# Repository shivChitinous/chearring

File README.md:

# chearring

Project to generate <1 cm charlieplexed grid of leds with ch32v003 based on https://mitxela.com/projects/ledstud. 

Project designed in Autodesk Fusion with schematic design in KiCad based on code from [kikad-skip](https://github.com/psychogenic/kicad-skip). 

Includes an Autodesk/EAGLE library with symbols, footprints and 3d designs for the following components: 

1. ### CH32V003F4U6 (QFN20)
2. ### 0201 LED
3. ### 0603 SMD capacitor

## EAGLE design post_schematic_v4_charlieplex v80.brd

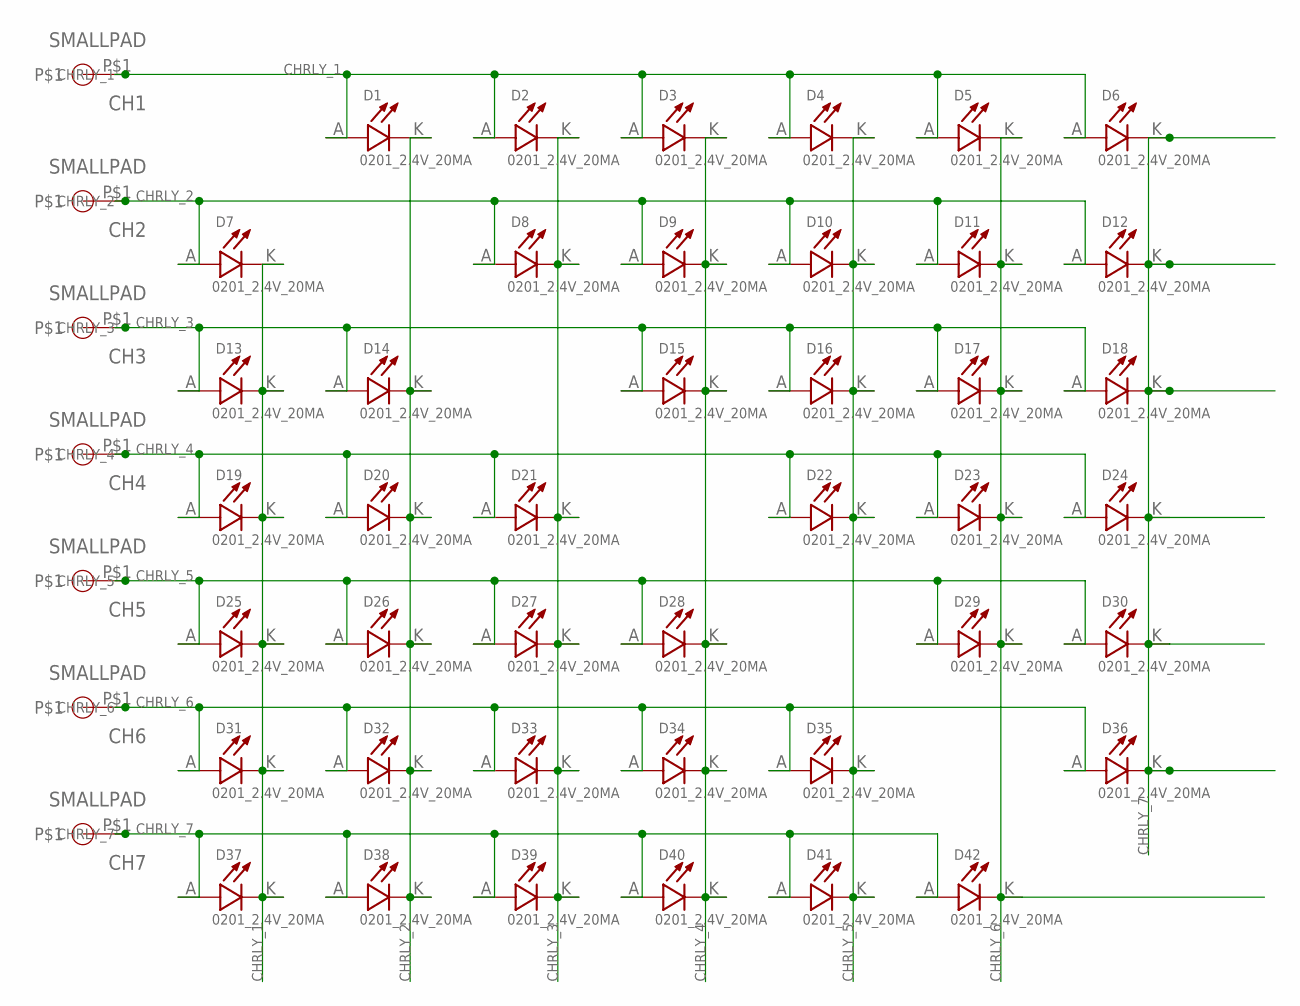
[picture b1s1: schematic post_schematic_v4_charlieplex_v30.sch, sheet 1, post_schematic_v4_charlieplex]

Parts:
CH1, CH2, CH3, CH4, CH5, CH6, CH7: SMALLPAD
D1, D2, D3, D4, D5, D6, D7, D8, D9, D10, D11, D12, D13, D14, D15, D16, D17, D18, D19, D20, D21, D22, D23, D24, D25, D26, D27, D28, D29, D30, D31, D32, D33, D34, D35, D36, D37, D38, D39, D40, D41, D42: 0201_2.4V_20MA

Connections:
CHRLY_1: CH1.P$1, D1.A, D2.A, D3.A, D4.A, D5.A, D6.A, D7.K, D13.K, D19.K, D25.K, D31.K, D37.K
CHRLY_2: CH2.P$1, D1.K, D7.A, D8.A, D9.A, D10.A, D11.A, D12.A, D14.K, D20.K, D26.K, D32.K, D38.K
CHRLY_3: CH3.P$1, D2.K, D8.K, D13.A, D14.A, D15.A, D16.A, D17.A, D18.A, D21.K, D27.K, D33.K, D39.K
CHRLY_4: CH4.P$1, D3.K, D9.K, D15.K, D19.A, D20.A, D21.A, D22.A, D23.A, D24.A, D28.K, D34.K, D40.K
CHRLY_5: CH5.P$1, D4.K, D10.K, D16.K, D22.K, D25.A, D26.A, D27.A, D28.A, D29.A, D30.A, D35.K, D41.K
CHRLY_6: CH6.P$1, D5.K, D11.K, D17.K, D23.K, D29.K, D31.A, D32.A, D33.A, D34.A, D35.A, D36.A, D42.K
CHRLY_7: CH7.P$1, D6.K, D12.K, D18.K, D24.K, D30.K, D36.K, D37.A, D38.A, D39.A, D40.A, D41.A, D42.A

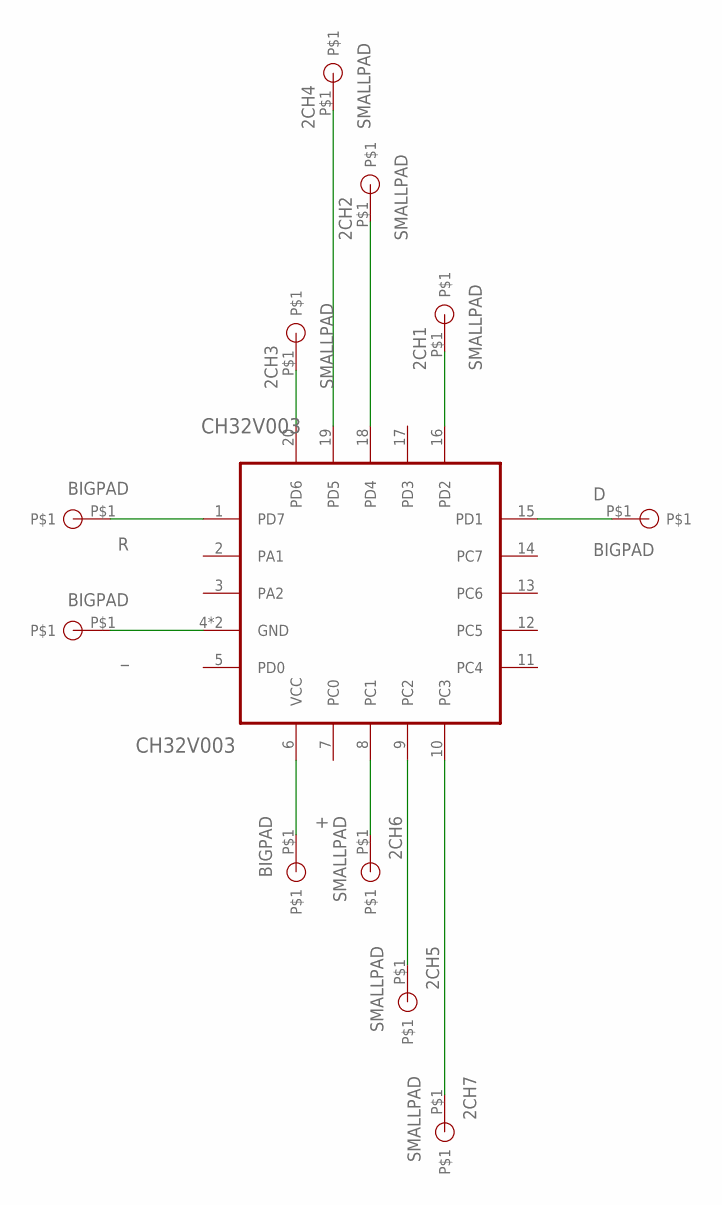
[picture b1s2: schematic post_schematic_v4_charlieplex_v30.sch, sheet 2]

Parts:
2CH1, 2CH2, 2CH3, 2CH4, 2CH5, 2CH6, 2CH7: SMALLPAD
+: BIGPAD
CH32V003: CH32V003; QFN40P300X300X90-21N
D: BIGPAD
R: BIGPAD
_: BIGPAD

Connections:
unnamed: +.P$1, CH32V003.6 (VCC)
unnamed: CH32V003.4 (GND), CH32V003.21 (GND), _.P$1
unnamed: CH32V003.1 (PD7), R.P$1
unnamed: CH32V003.15 (PD1), D.P$1
unnamed: 2CH1.P$1, CH32V003.16 (PD2)
unnamed: 2CH2.P$1, CH32V003.18 (PD4)
unnamed: 2CH3.P$1, CH32V003.20 (PD6)
unnamed: 2CH4.P$1, CH32V003.19 (PD5)
unnamed: 2CH6.P$1, CH32V003.8 (PC1)
unnamed: 2CH5.P$1, CH32V003.9 (PC2)
unnamed: 2CH7.P$1, CH32V003.10 (PC3)

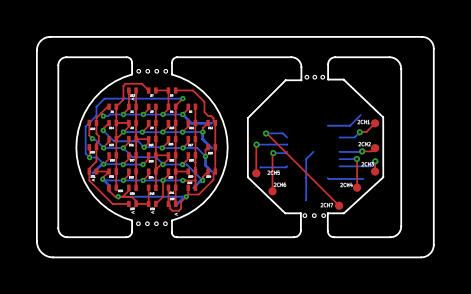
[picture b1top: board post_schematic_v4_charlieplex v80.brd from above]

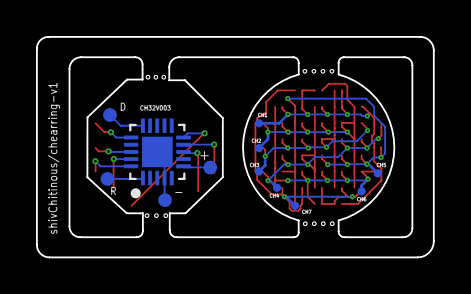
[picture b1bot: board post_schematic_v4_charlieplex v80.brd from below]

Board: 2 copper layers, 22.0 x 12.2 mm, 61 parts (12 on the bottom side), 18 nets.

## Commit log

2025-01-25 Creating functions and adding a jupyter notebook
2025-01-28 CAD
    Added gerber files, eagle cad file. All modeling was done in fusion 360.
2025-01-29 New version with capacitor, final board and updated readme
    Library files added
2025-01-29 modify gitignore
2025-01-29 Create LICENSE
2025-01-29 remove unnecessary file
2025-01-29 update gitignore
2025-02-05 Simulations for animating the led board and saving header files that store the animations and the fonts
